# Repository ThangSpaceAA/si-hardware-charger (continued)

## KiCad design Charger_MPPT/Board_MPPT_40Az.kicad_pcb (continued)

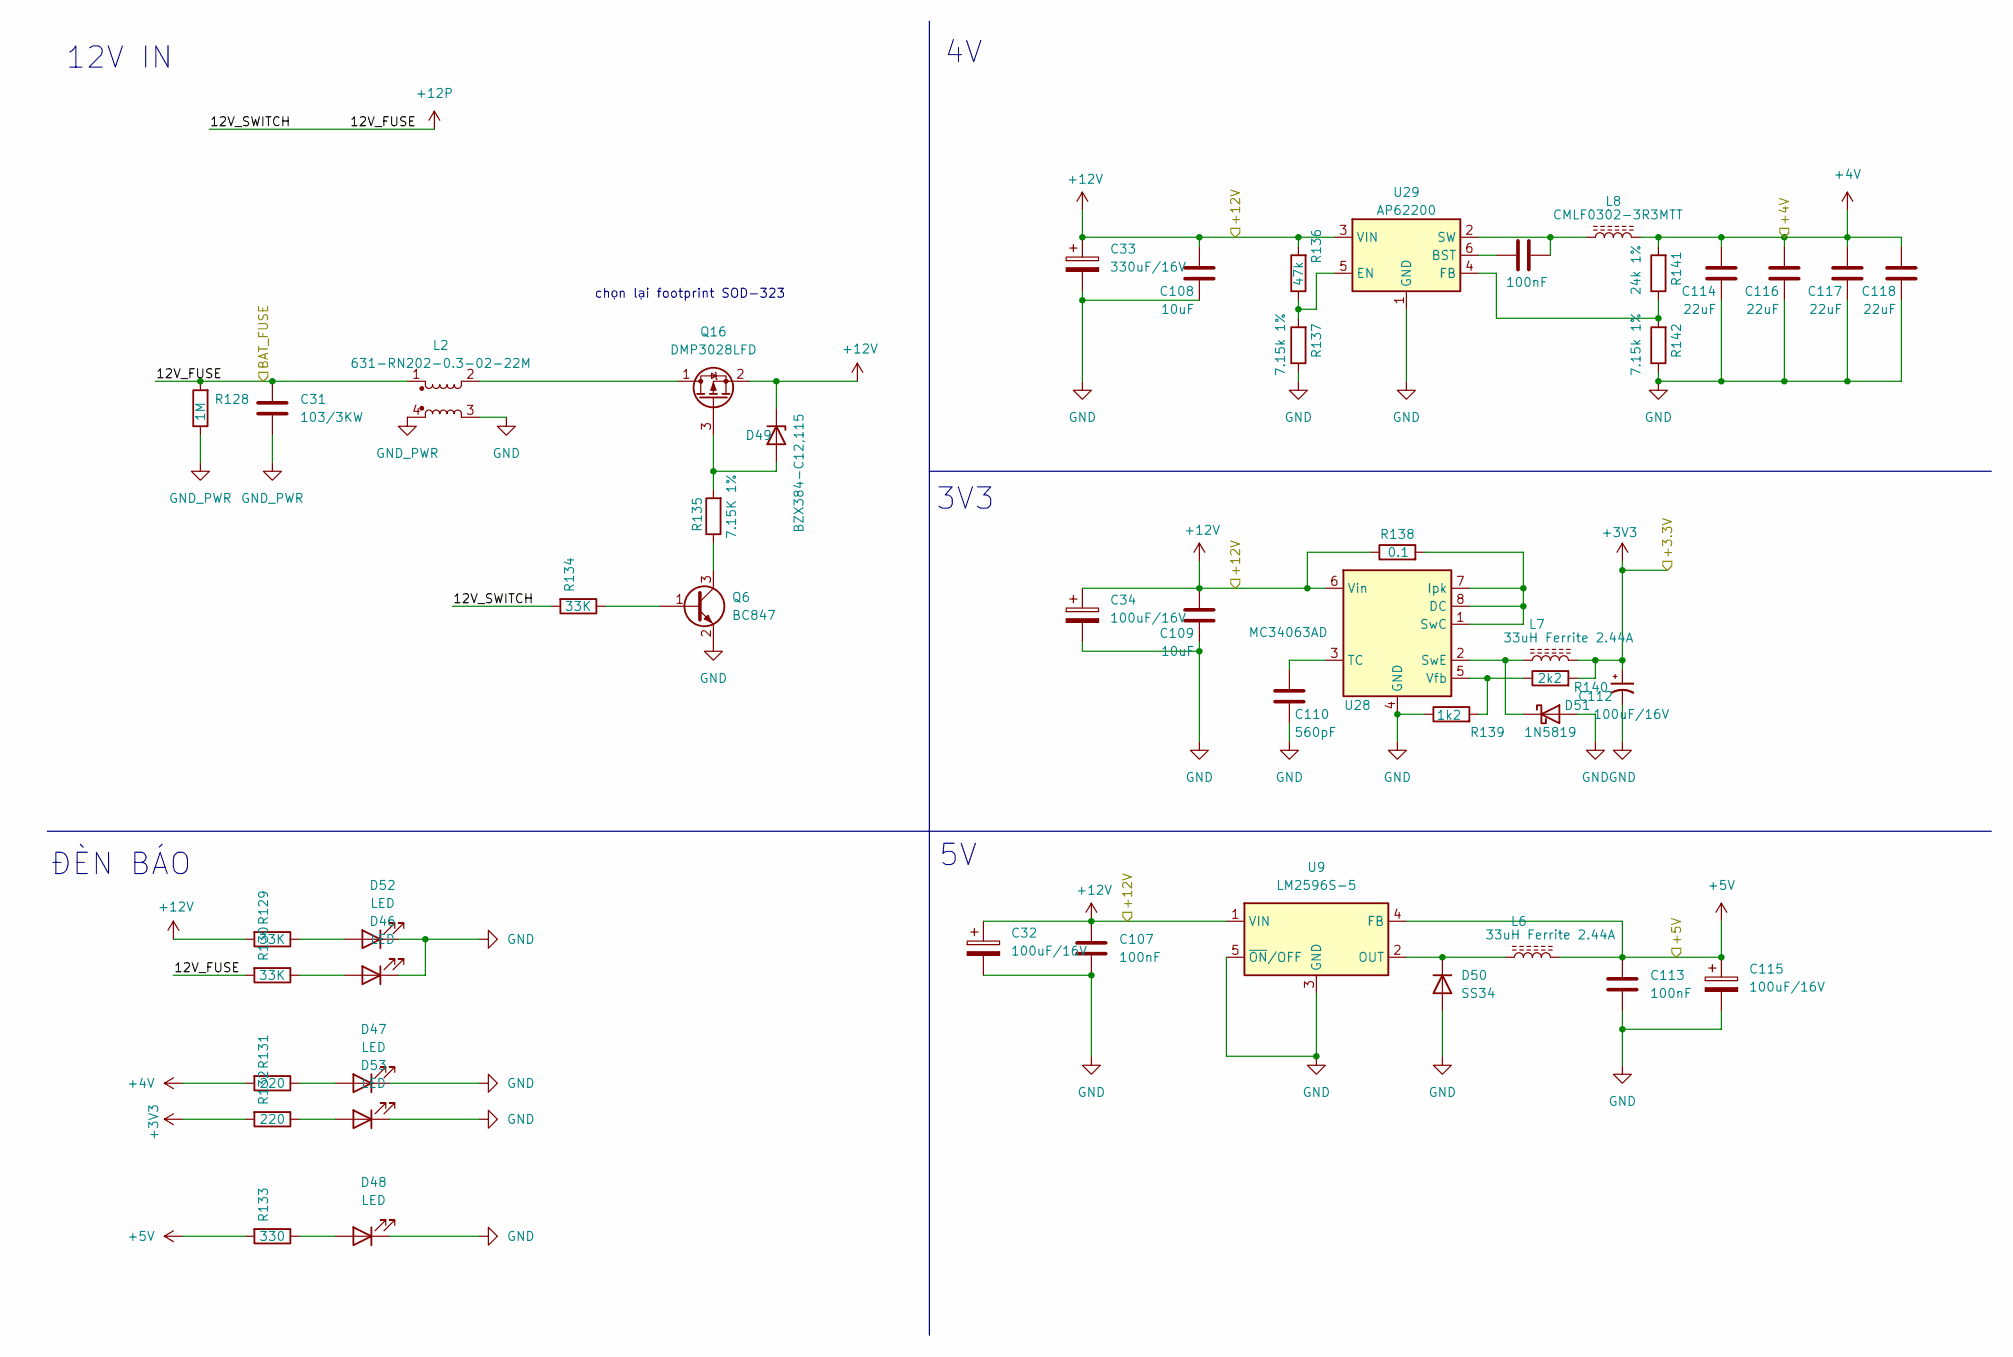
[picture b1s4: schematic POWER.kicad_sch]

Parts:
C31: 103/3KW; C_Disc_D7.0mm_W2.5mm_P5.00mm
C32, C34: 100uF/16V; CP_EIA-6032-28_Kemet-C_Pad2.25x2.35mm_HandSolder
C33: 330uF/16V; CP_EIA-6032-28_Kemet-C_Pad2.25x2.35mm_HandSolder
C107, C111, C113: 100nF; C_0805_2012Metric
C108, C109: 10uF; C_0805_2012Metric
C110: 560pF; C_0805_2012Metric
C112: 100uF/16V; CP_EIA-6032-20_AVX-F_Pad2.25x2.35mm_HandSolder
C114, C116, C117, C118: 22uF; C_0805_2012Metric
C115: 100uF/16V; CP_EIA-6032-15_Kemet-U
D46, D47, D48, D52, D53: LED; LED_0805_2012Metric
D49: BZX384-C12,115; D_SOD-323_HandSoldering
D50: SS34; D_SMA
D51: 1N5819; D_SOD-123F
L2: 631-RN202-0.3-02-22M; Choke_Schaffner_RN202-04-8.8x18.2mm
L6, L7: 33uH Ferrite 2.44A; L_Taiyo-Yuden_NR-60xx
L8: CMLF0302-3R3MTT; L_Wurth_WE-LQSH-3012
Q6: BC847; SOT-23
Q16: DMP3028LFD; TO-252-2
R128: 1M; R_0805_2012Metric
R129, R130, R134: 33K; R_0805_2012Metric
R131, R132: 220; R_0805_2012Metric
R133: 330; R_0805_2012Metric
R135: 7.15K 1%; R_0805_2012Metric
R136: 47k; R_0805_2012Metric
R137, R142: 7.15k 1%; R_0402_1005Metric
R138: 0.1; R_1206_3216Metric
R139: 1k2; R_0805_2012Metric
R140: 2k2; R_0805_2012Metric
R141: 24k 1%; R_0805_2012Metric
U9: LM2596S-5; TO-263-5_TabPin3
U28: MC34063AD; SOIC-8_3.9x4.9mm_P1.27mm
U29: AP62200; TSOT-26

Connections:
+3V3: C112.1, L7.2, R132.2, R140.2; also elsewhere on the board
+4V: C114.1, C116.1, C117.1, C118.1, L8.2, R131.2, R141.2; also elsewhere on the board
+5V: C113.1, C115.1, L6.2, R133.2, U9.4 (FB); also elsewhere on the board
+12V: C32.1, C33.1, C34.1, C107.1, C108.1, C109.1, D49.1 (K), Q16.2 (S), R129.2, R136.2, R138.1, U9.1 (VIN), U28.6 (Vin), U29.3 (VIN); also elsewhere on the board
BAT +: C31.1, L2.1, R128.2, R130.2, R134.2; also elsewhere on the board
GND: C32.2, C33.2, C34.2, C107.2, C108.2, C109.2, C110.2, C112.2, C113.2, C114.2, C115.2, C116.2, C117.2, C118.2, D46.1 (K), D47.1 (K), D48.1 (K), D50.2 (A), D51.2 (A), D52.1 (K), D53.1 (K), L2.3, Q6.2 (E), R137.1, R139.1, R142.1, U9.3 (GND), U9.5 (~ON/OFF), U28.4 (GND), U29.1 (GND); also elsewhere on the board
GND_PWR: C31.2, L2.4, R128.1
unnamed: D46.2 (A), R130.1
unnamed: D47.2 (A), R131.1
unnamed: D48.2 (A), R133.1
unnamed: D49.2 (A), Q16.3 (G), R135.2
unnamed: D50.1 (K), L6.1, U9.2 (OUT)
unnamed: D51.1 (K), L7.1, U28.2 (SwE)
unnamed: D52.2 (A), R129.1
unnamed: D53.2 (A), R132.1
unnamed: Q6.1 (B), R134.1
unnamed: Q6.3 (C), R135.1
unnamed: L2.2, Q16.1 (D)
unnamed: R138.2, U28.1 (SwC), U28.7 (Ipk), U28.8 (DC)
unnamed: C110.1, U28.3 (TC)
unnamed: R139.2, R140.1, U28.5 (Vfb)
unnamed: C111.2, U29.6 (BST)
unnamed: R136.1, R137.2, U29.5 (EN)
unnamed: R141.1, R142.2, U29.4 (FB)
unnamed: C111.1, L8.1, U29.2 (SW)

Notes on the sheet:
12V IN
chọn lại footprint SOD-323
3V3
ĐÈN BÁO

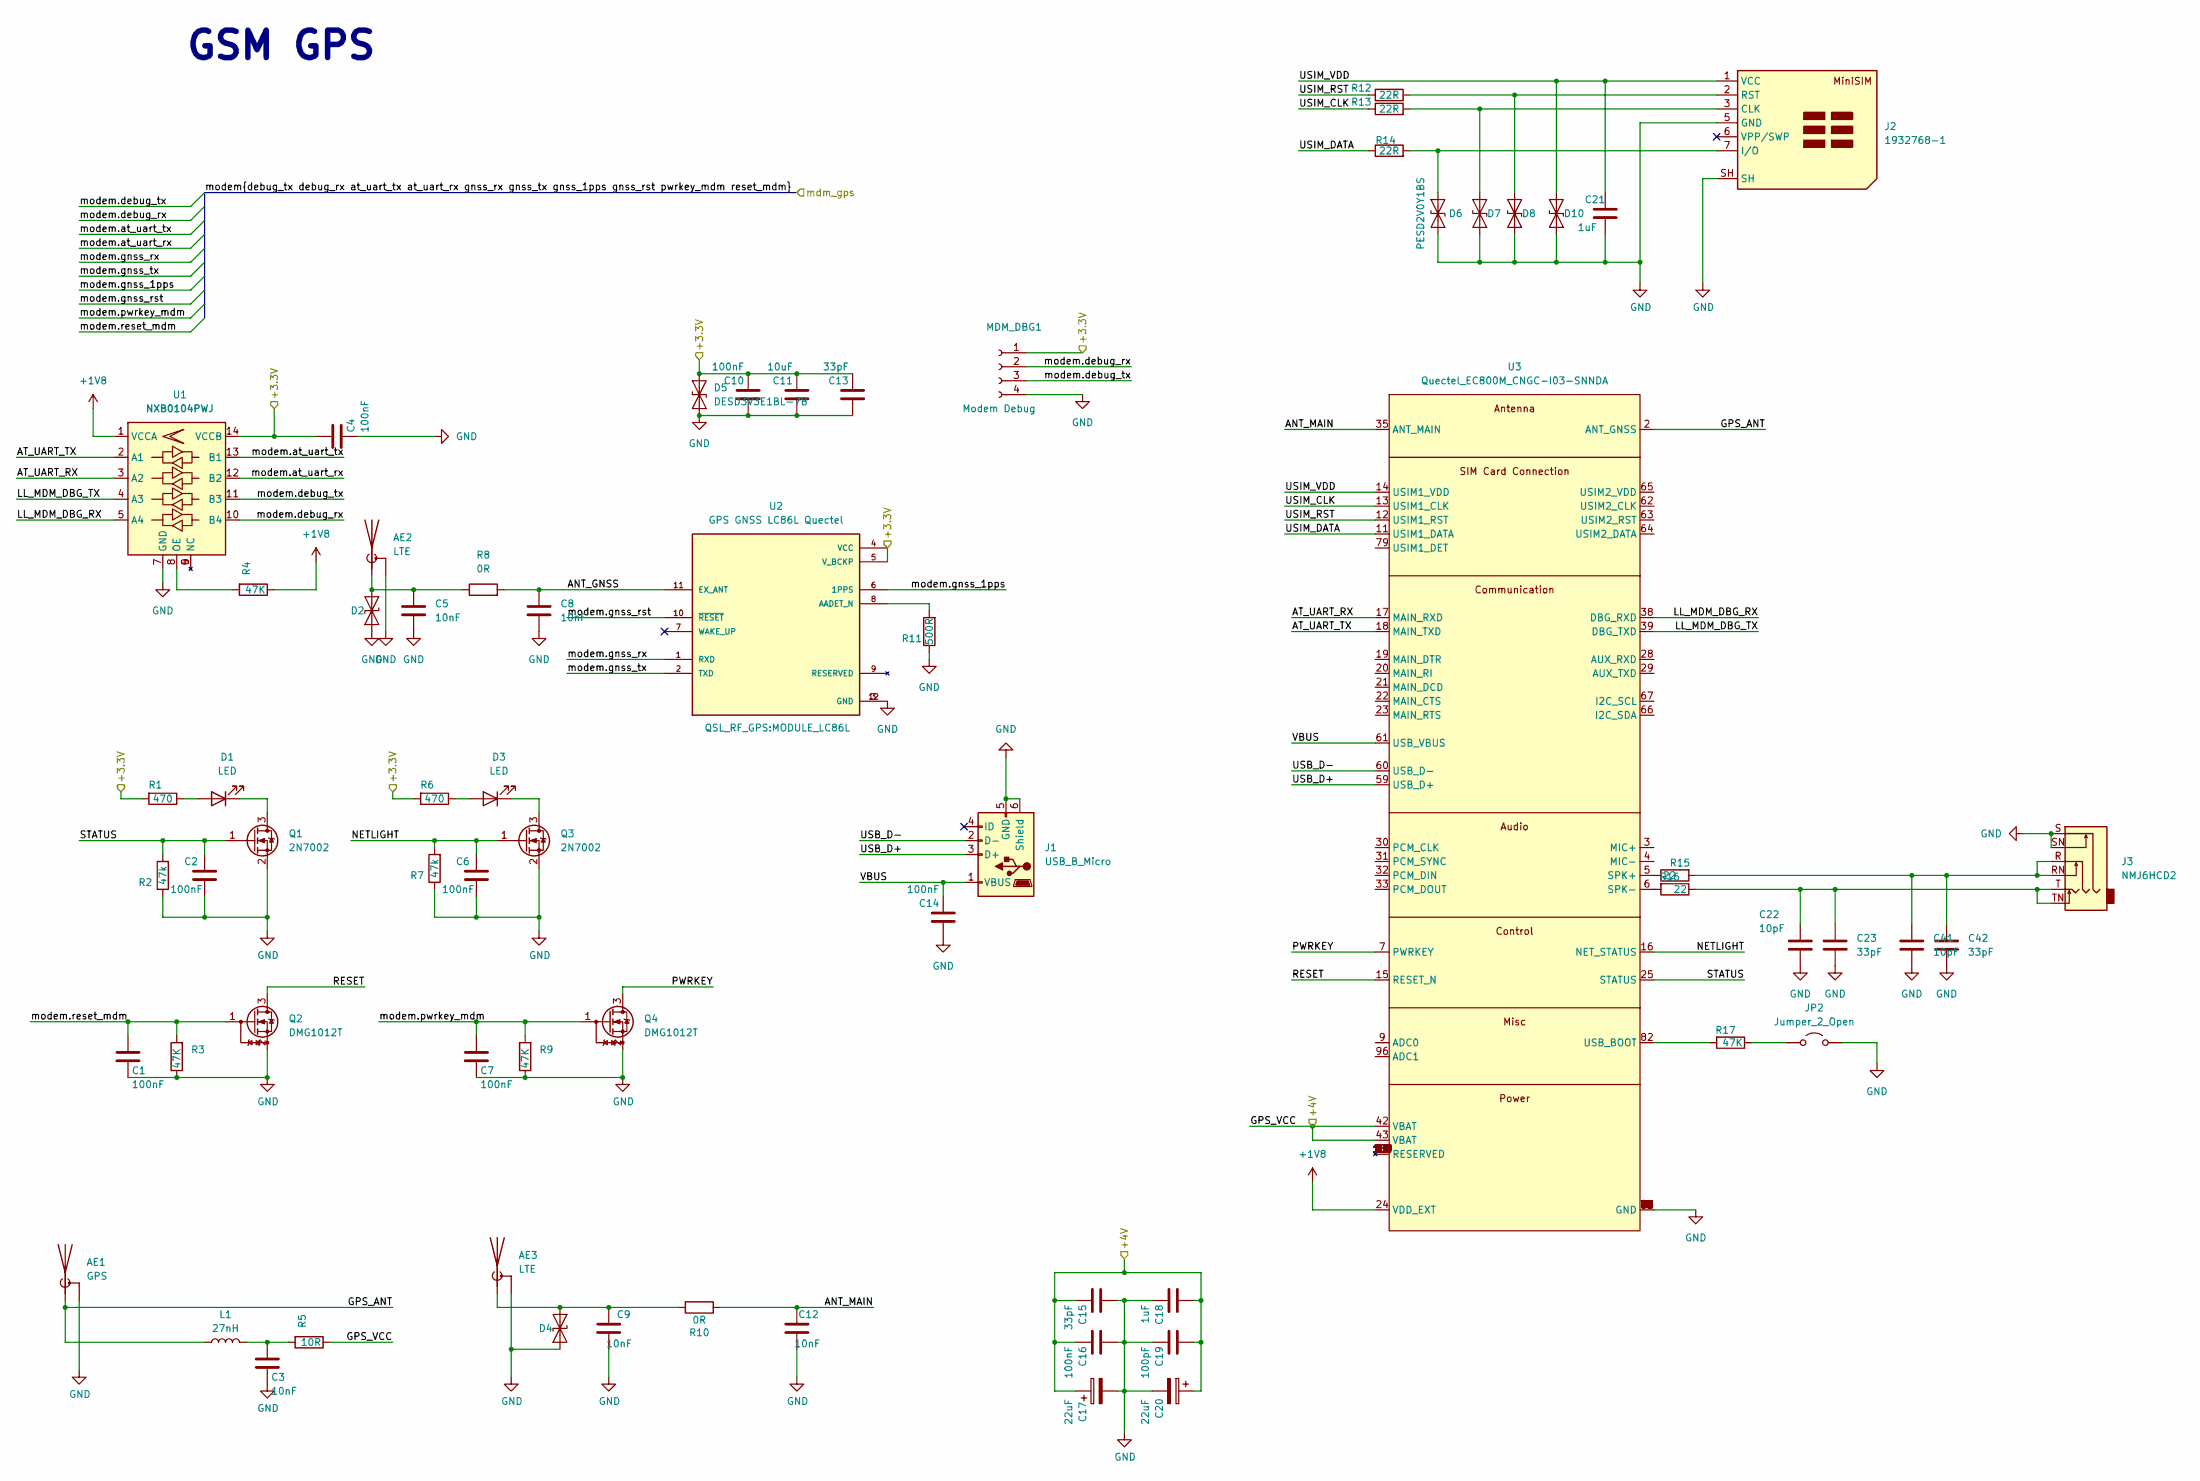
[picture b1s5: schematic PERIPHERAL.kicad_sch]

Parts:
AE1: GPS; SMA_Amphenol_132289_EdgeMount
AE2: LTE; SMA_Amphenol_A-4JA
AE3: LTE; SMA_Amphenol_132289_EdgeMount
C1, C2, C4, C6, C7, C10, C14, C16: 100nF; C_0805_2012Metric
C3, C9, C12: 10nF; C_0805_2012Metric
C5, C8: 10nF; C_0603_1608Metric
C11: 10uF; C_0805_2012Metric
C13, C15: 33pF; C_0805_2012Metric
C17, C20: 22uF; CP_EIA-3216-12_Kemet-S
C18, C21: 1uF; C_0805_2012Metric
C19: 100pF; C_0805_2012Metric
C22, C41: 10pF; C_0603_1608Metric
C23, C42: 33pF; C_0603_1608Metric
D1, D3: LED; LED_0805_2012Metric
D2, D4, D6, D7, D8, D10: PESD2V0Y1BS; D_0201_0603Metric
D5: DESD3V3E1BL-7B; CTS_D_0402_1005Metric
J1: USB_B_Micro; USB_Micro-B_Amphenol_10118194_Horizontal
J2: 1932768-1; nanoSIM_Hinged_CUI_NSIM-2-C
J3: NMJ6HCD2; Jack_3.5mm_CUI_SJ2-3593D-SMT_Horizontal
JP2: Jumper_2_Open; SolderJumper-2_P1.3mm_Open_Pad1.0x1.5mm
L1: 27nH; L_0603_1608Metric
MDM_DBG1: Modem Debug; Molex_PicoBlade_53047-0410_1x04_P1.25mm_Vertical
Q1, Q3: 2N7002; SOT-23
Q2, Q4: DMG1012T; SOT-523
R1, R6: 470; R_0805_2012Metric
R2, R7: 47k; R_0805_2012Metric
R3, R4, R9, R17: 47K; R_0805_2012Metric
R5: 10R; R_0805_2012Metric
R8: 0R; R_0603_1608Metric
R10: 0R; R_0805_2012Metric
R11: 500R; R_0805_2012Metric
R12, R13, R14: 22R; R_0805_2012Metric
R15, R16: 22; R_0603_1608Metric
U1: NXB0104PWJ; TSSOP-14-1EP_4.4x5mm_P0.65mm
U2: GPS GNSS LC86L Quectel; MODULE_LC86L; PARTREV V1.2
U3: Quectel_EC800M_CNGC-I03-SNNDA; Quectel_EC800M_CN

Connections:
+1V8: R4.1, U1.1 (VCCA), U3.24 (VDD_EXT)
+3V3: C4.1, C10.2, C11.2, C13.2, D5.2 (A2), MDM_DBG1.1, R1.2, R6.2, U1.14 (VCCB), U2.4 (VCC), U2.5 (V_BCKP); also elsewhere on the board
+4V: C15.2, C16.2, C17.1, C18.1, C19.1, C20.1, R5.1, U3.42 (VBAT), U3.43 (VBAT); also elsewhere on the board
/MCU/modem.at_uart_rx: U1.12 (B2); also elsewhere on the board
/MCU/modem.at_uart_tx: U1.13 (B1); also elsewhere on the board
/MCU/modem.debug_rx: MDM_DBG1.2, U1.10 (B4)
/MCU/modem.debug_tx: MDM_DBG1.3, U1.11 (B3)
/MCU/modem.gnss_1pps: U2.6 (1PPS); also elsewhere on the board
/MCU/modem.gnss_rst: U2.10 (~RESET); also elsewhere on the board
/MCU/modem.gnss_rx: U2.1 (RXD); also elsewhere on the board
/MCU/modem.gnss_tx: U2.2 (TXD); also elsewhere on the board
/MCU/modem.pwrkey_mdm: C7.1, Q4.1 (G), R9.2; also elsewhere on the board
/MCU/modem.reset_mdm: C1.1, Q2.1 (G), R3.2; also elsewhere on the board
/MDM_SIM/ANT_GNSS: C8.1, R8.2, U2.11 (EX_ANT)
/MDM_SIM/ANT_MAIN: C12.2, R10.1, U3.35 (ANT_MAIN)
/MDM_SIM/AT_UART_RX: U1.3 (A2), U3.17 (MAIN_RXD)
/MDM_SIM/AT_UART_TX: U1.2 (A1), U3.18 (MAIN_TXD)
/MDM_SIM/GPS_ANT: AE1.1 (A), L1.1, U3.2 (ANT_GNSS)
/MDM_SIM/LL_MDM_DBG_RX: U1.5 (A4), U3.38 (DBG_RXD)
/MDM_SIM/LL_MDM_DBG_TX: U1.4 (A3), U3.39 (DBG_TXD)
/MDM_SIM/NETLIGHT: C6.2, Q3.1 (G), R7.2, U3.16 (NET_STATUS)
/MDM_SIM/PWRKEY: Q4.3 (D), U3.7 (PWRKEY)
/MDM_SIM/RESET: Q2.3 (D), U3.15 (RESET_N)
/MDM_SIM/STATUS: C2.2, Q1.1 (G), R2.2, U3.25 (STATUS)
/MDM_SIM/USB_D+: J1.3 (D+), U3.59 (USB_D+)
/MDM_SIM/USB_D-: J1.2 (D-), U3.60 (USB_D-)
/MDM_SIM/USIM_CLK: R13.1, U3.13 (USIM1_CLK)
/MDM_SIM/USIM_DATA: R14.1, U3.11 (USIM1_DATA)
/MDM_SIM/USIM_RST: R12.1, U3.12 (USIM1_RST)
/MDM_SIM/USIM_VDD: C21.2, D10.2 (A2), J2.1 (VCC), U3.14 (USIM1_VDD)
/MDM_SIM/VBUS: C14.2, J1.1 (VBUS), U3.61 (USB_VBUS)
GND: AE1.2 (Shield), AE2.2 (Shield), AE3.2 (Shield), C1.2, C2.1, C3.2, C4.2, C5.2, C6.1, C7.2, C8.2, C9.1, C10.1, C11.1, C12.1, C13.1, C14.1, C15.1, C16.1, C17.2, C18.2, C19.2, C20.2, C21.1, C22.2, C23.2, C41.2, C42.2, D2.1 (A1), D4.1 (A1), D5.1 (A1), D6.1 (A1), D7.1 (A1), D8.1 (A1), D10.1 (A1), J1.5 (GND), J1.6 (Shield), J2.5 (GND), J2.SH, J3.S, J3.SN, JP2.2 (B), MDM_DBG1.4, Q1.2 (S), Q2.2 (S), Q3.2 (S), Q4.2 (S), R2.1, R3.1, R7.1, R9.1, R11.1, U1.7 (GND), U2.3 (GND), U2.12 (GND), U3.1 (GND), U3.10 (GND), U3.27 (GND), U3.34 (GND), U3.36 (GND), U3.37 (GND), U3.40 (GND), U3.41 (GND), U3.45 (GND), U3.46 (GND), U3.47 (GND), U3.48 (GND), U3.70 (GND), U3.71 (GND), U3.72 (GND), U3.73 (GND), U3.88 (GND), U3.89 (GND), U3.90 (GND), U3.91 (GND), U3.92 (GND), U3.93 (GND), U3.94 (GND), U3.95 (GND); also elsewhere on the board
unnamed: AE2.1 (A), C5.1, D2.2 (A2), R8.1
unnamed: AE3.1 (A), C9.2, D4.2 (A2), R10.2
unnamed: C3.1, L1.2, R5.2
unnamed: C22.1, C23.1, J3.T, J3.TN, R16.1
unnamed: C41.1, C42.1, J3.R, J3.RN, R15.2
unnamed: D1.2 (A), R1.1
unnamed: D1.1 (K), Q1.3 (D)
unnamed: D3.2 (A), R6.1
unnamed: D3.1 (K), Q3.3 (D)
unnamed: D6.2 (A2), J2.7 (I/O), R14.2
unnamed: D7.2 (A2), J2.3 (CLK), R13.2
unnamed: D8.2 (A2), J2.2 (RST), R12.2
unnamed: JP2.1 (A), R17.1
unnamed: R4.2, U1.8 (OE)
unnamed: R11.2, U2.8 (AADET_N)
unnamed: R15.1, U3.5 (SPK+)
unnamed: R16.2, U3.6 (SPK-)
unnamed: R17.2, U3.82 (USB_BOOT)

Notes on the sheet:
GSM GPS

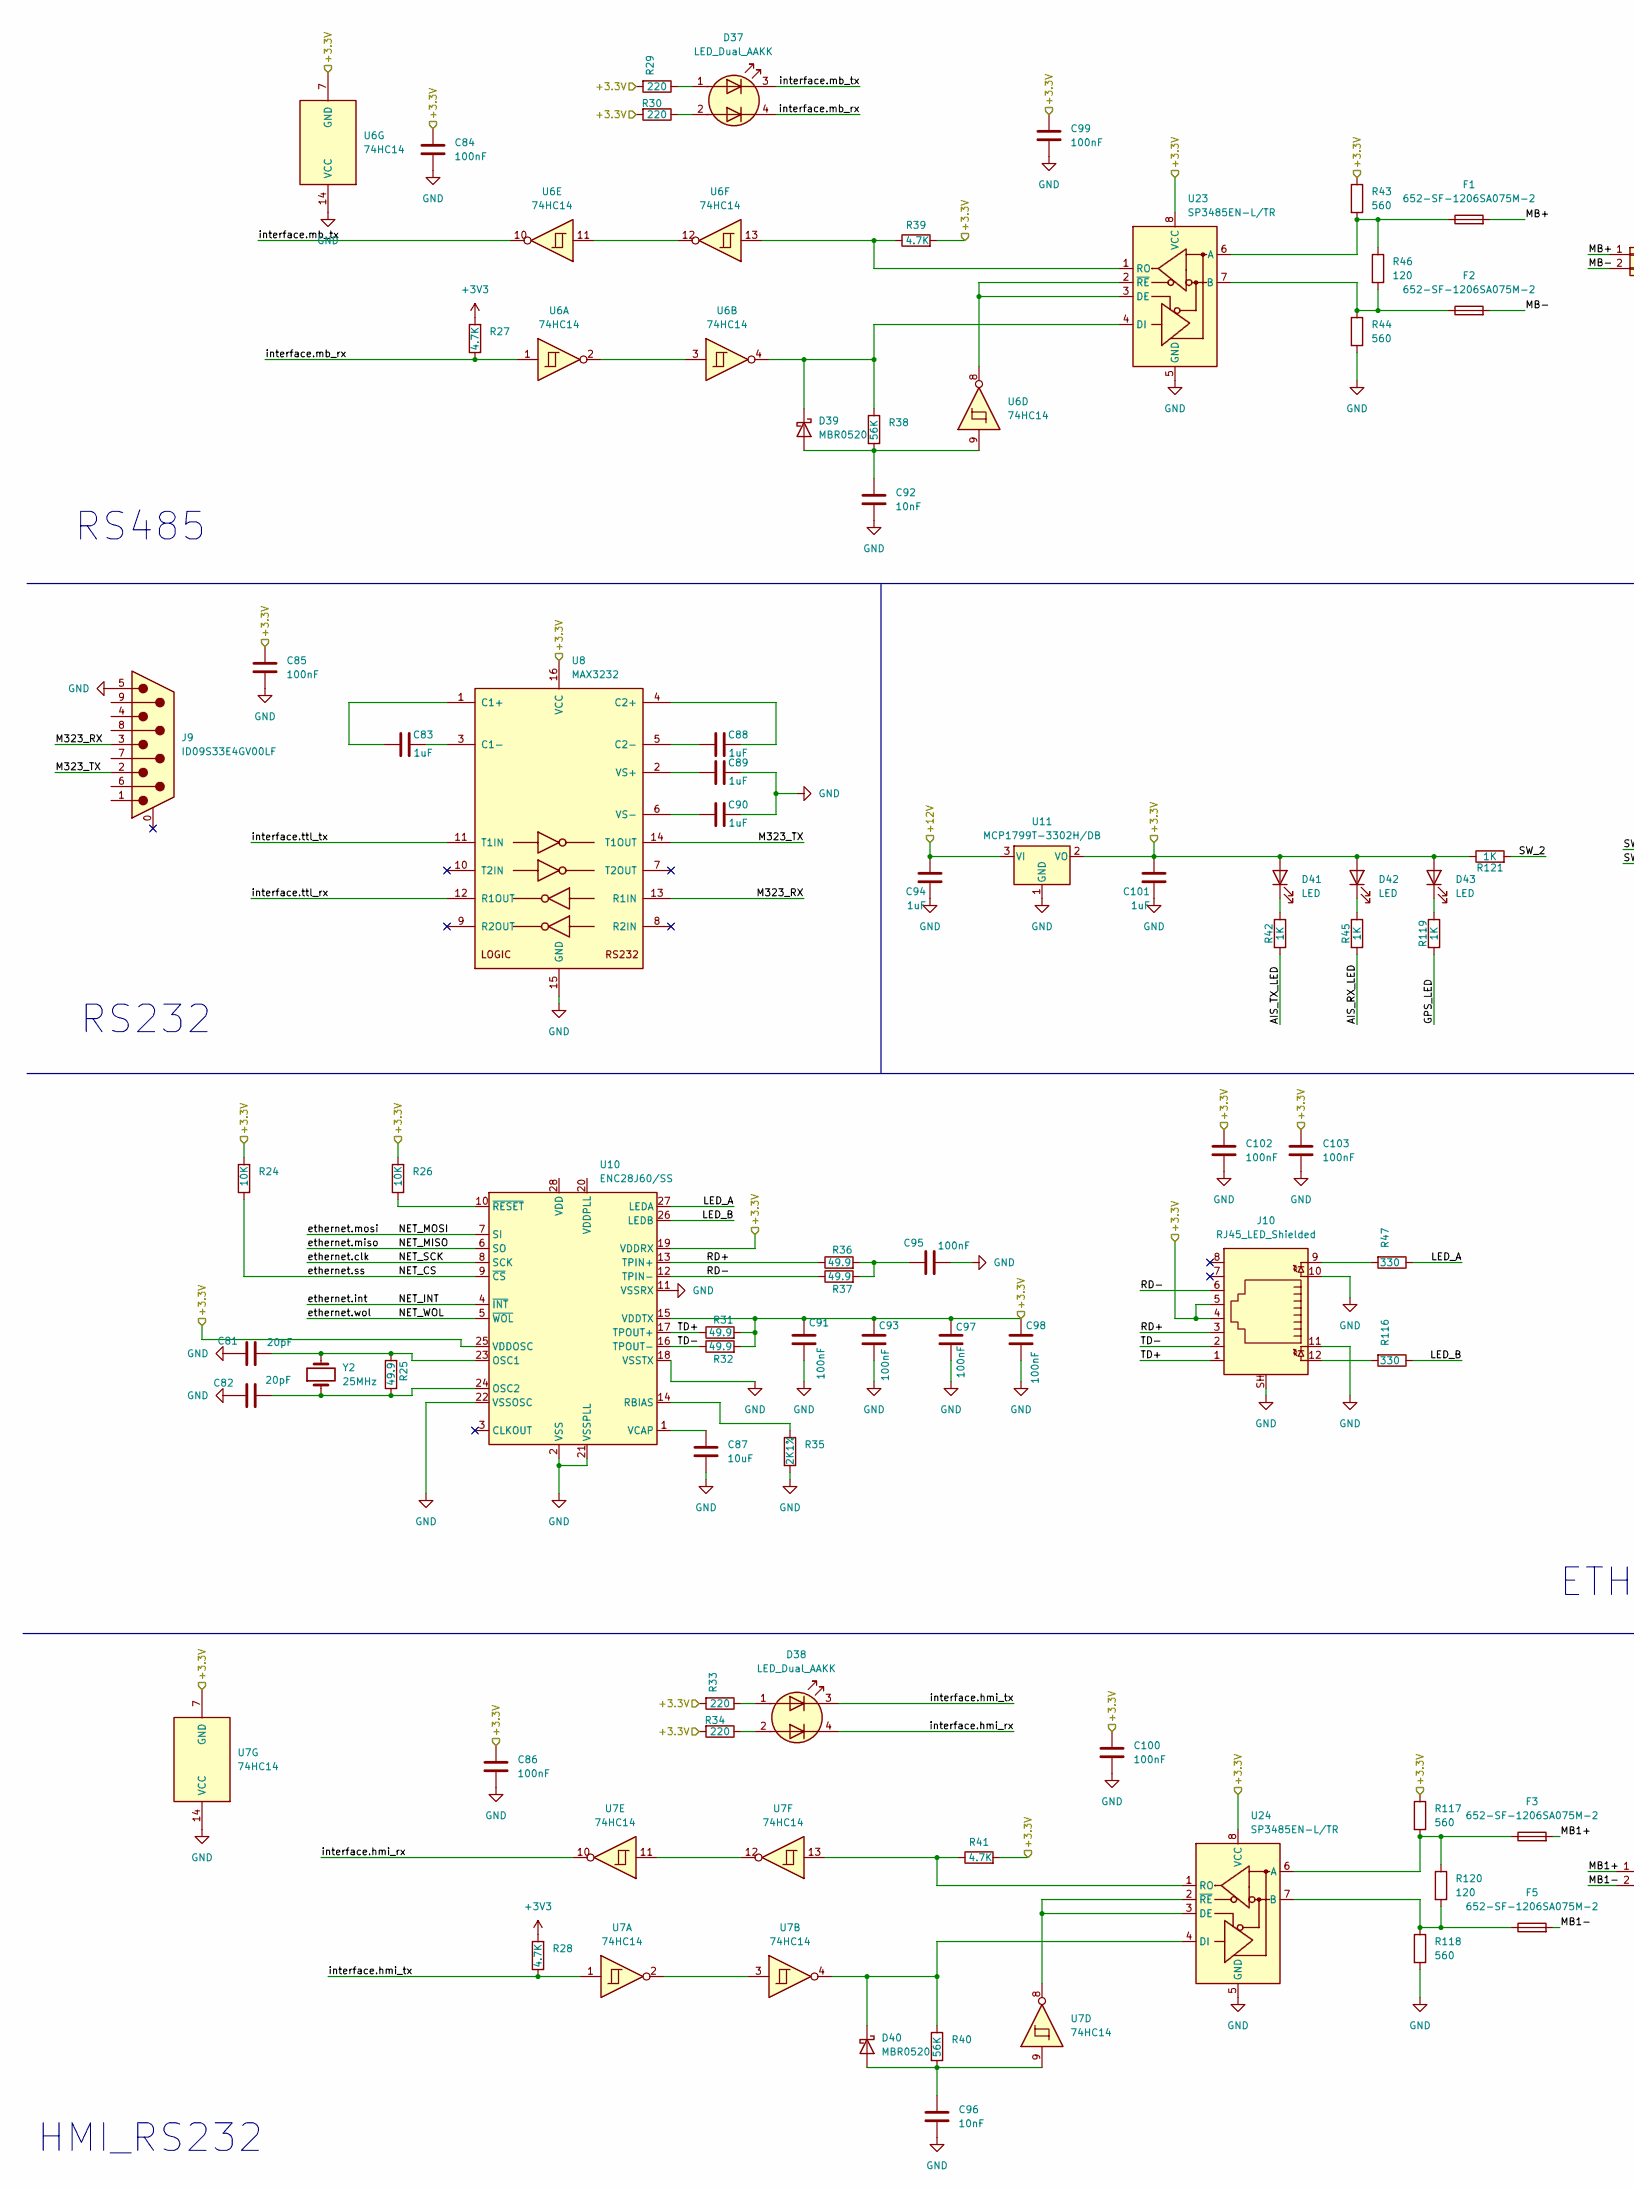
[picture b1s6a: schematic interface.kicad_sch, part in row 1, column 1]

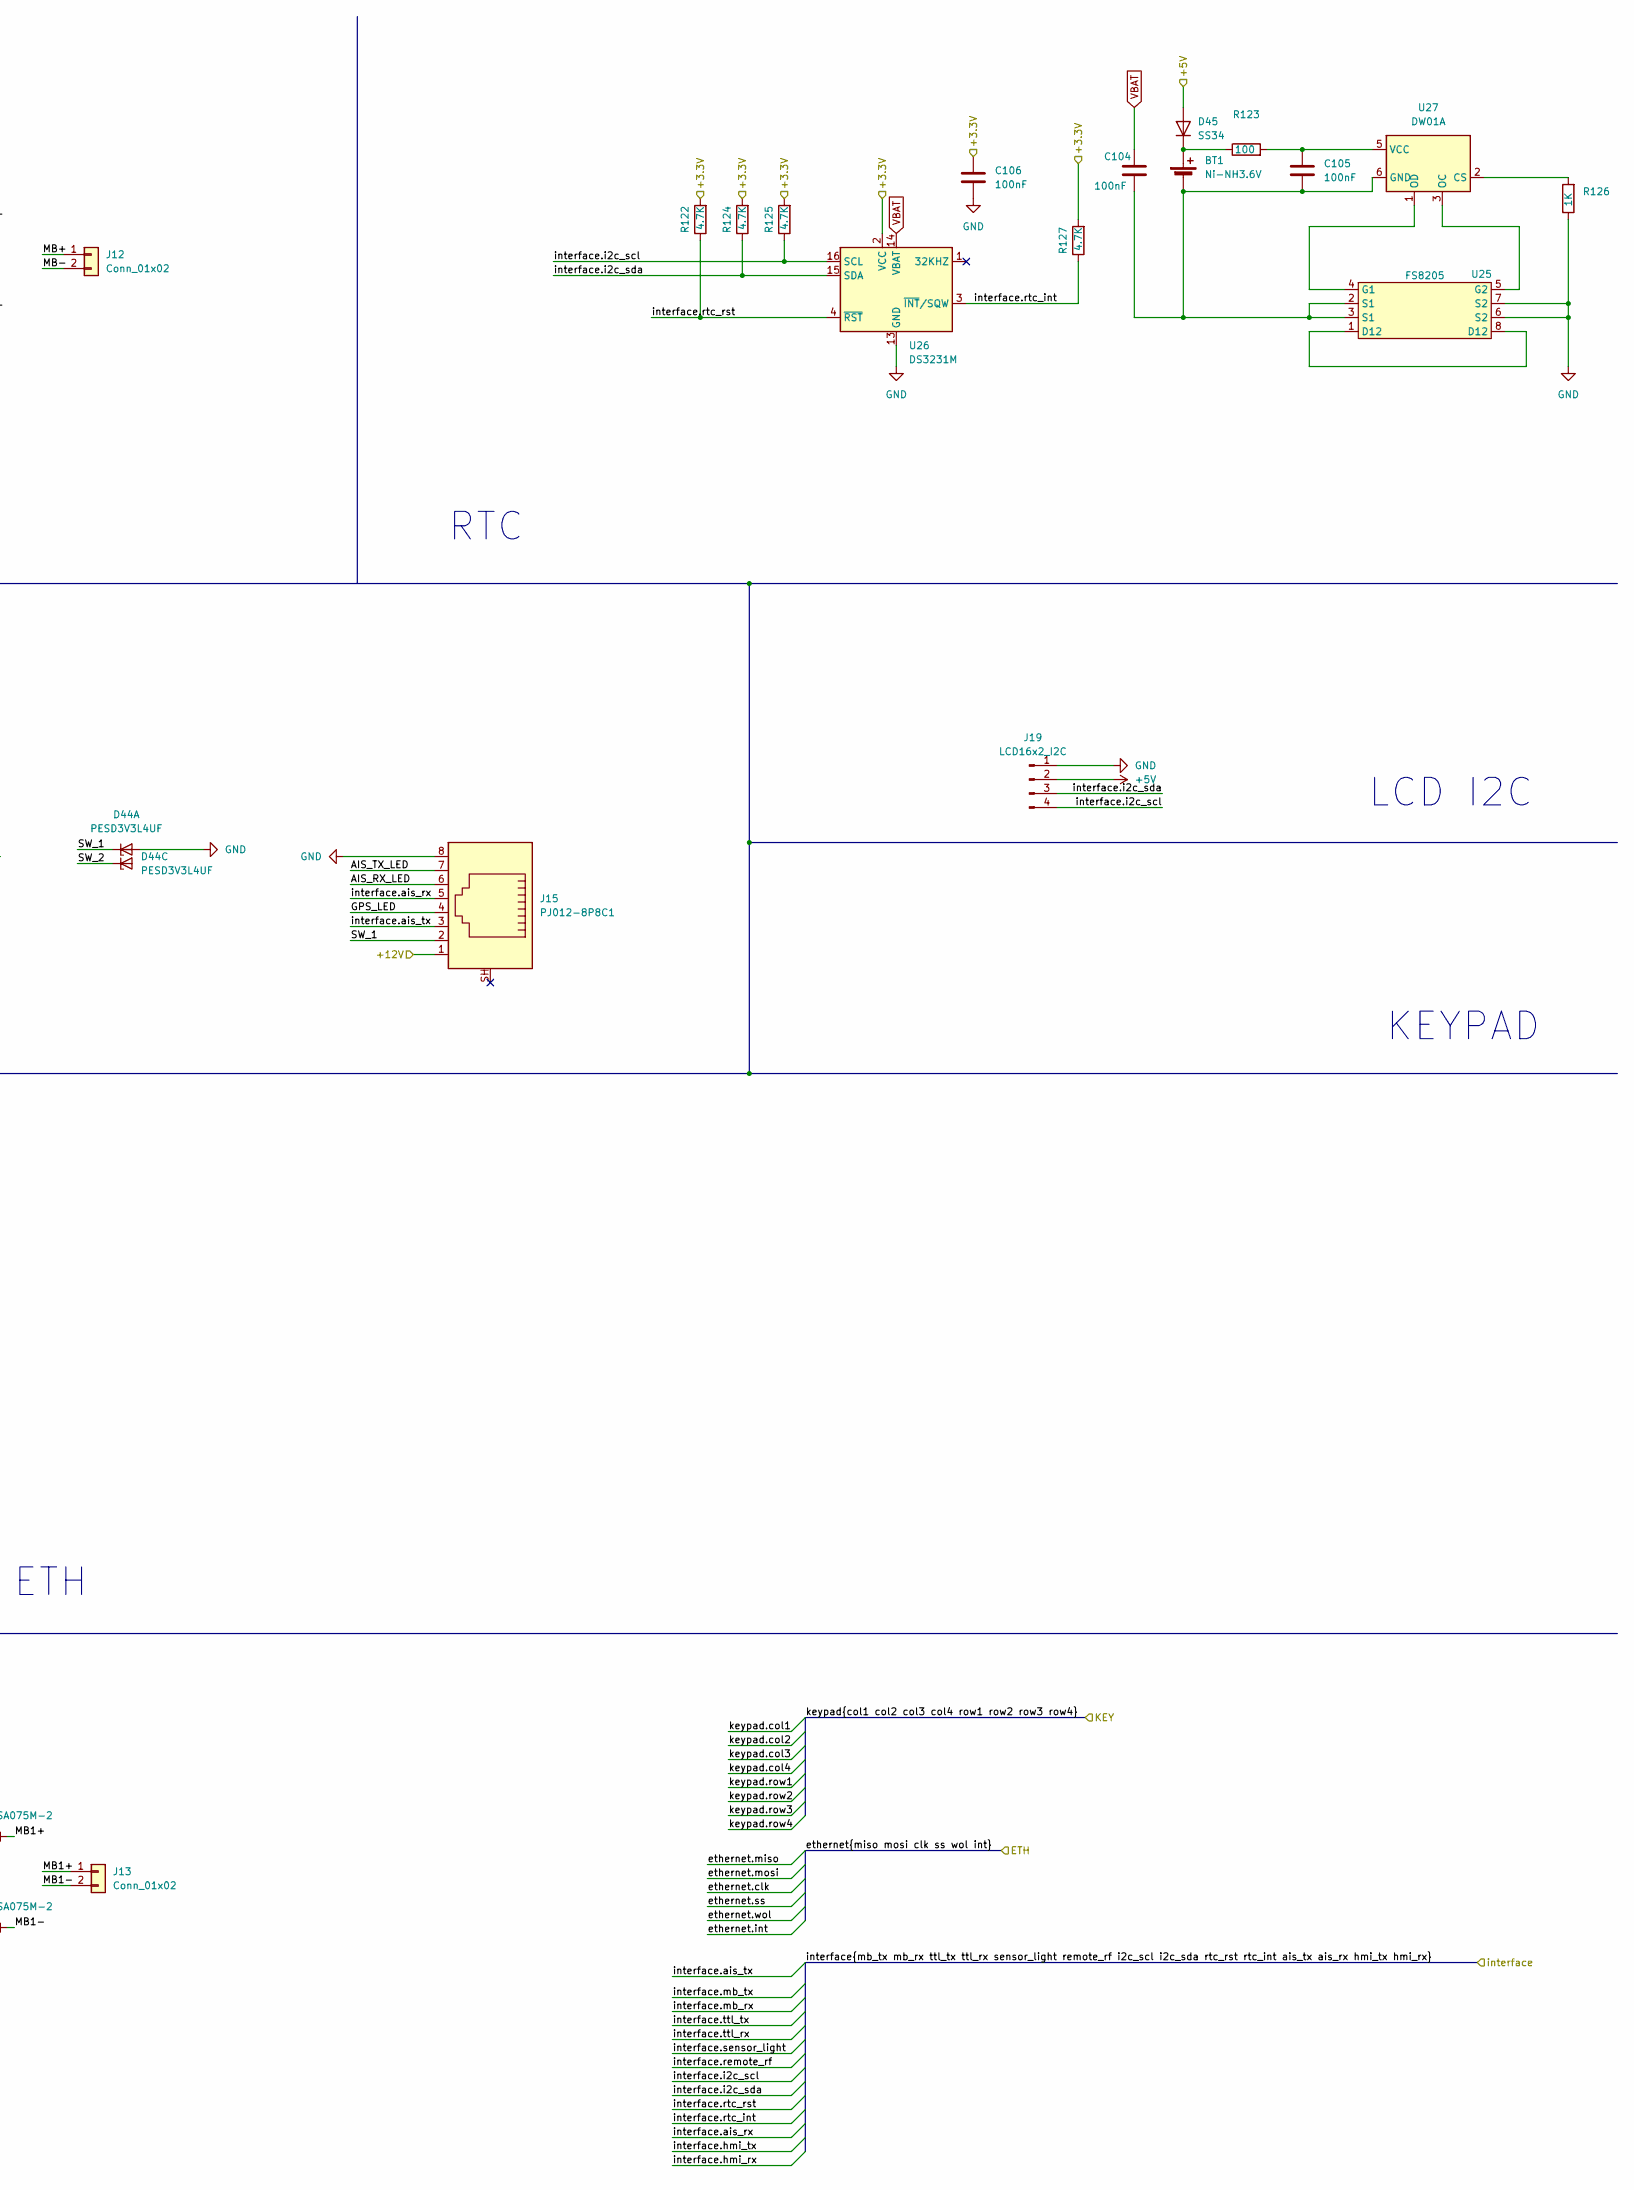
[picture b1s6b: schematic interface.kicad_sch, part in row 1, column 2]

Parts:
BT1: Ni-NH3.6V; NI-NH3.6V
C81, C82: 20pF; C_0402_1005Metric
C83, C88, C89, C90, C94, C101: 1uF; C_0805_2012Metric
C84, C85, C86, C91, C93, C95, C97, C98, C99, C100, C102, C103, C104, C105, C106: 100nF; C_0805_2012Metric
C87: 10uF; C_0805_2012Metric
C92, C96: 10nF; C_0805_2012Metric
D37, D38: LED_Dual_AAKK; LED_D3.0mmP2.54_2x2_Horizontal__ACAC
D39, D40: MBR0520; D_SOD-123
D41, D42, D43: LED; LED_0805_2012Metric
D44: PESD3V3L4UF; SOT-886
D45: SS34; D_SMA
F1, F2, F3, F5: 652-SF-1206SA075M-2; Fuse_1812_4532Metric
J9: ID09S33E4GV00LF; DSUB-9_Female_Horizontal_P2.77x2.84mm_EdgePinOffset4.94mm_H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
J10: RJ45_LED_Shielded; RJ45_Hanrun_HR911105A_Horizontal
J12, J13: Conn_01x02; TerminalBlock_Phoenix_MKDS-1,5-2-5.08_1x02_P5.08mm_Horizont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
J15: PJ012-8P8C1; RJ45_OST_PJ012-8P8CX_Vertical
J19: LCD16x2_I2C; PinHeader_1x04_P2.54mm_Vertical
R24, R26: 10K; R_0805_2012Metric
R25, R31, R32, R36, R37: 49.9; R_0805_2012Metric
R27, R28, R39, R41, R122, R124, R125, R127: 4.7K; R_0805_2012Metric
R29, R30, R33, R34: 220; R_0805_2012Metric
R35: 2K1%; R_0805_2012Metric
R38, R40: 56K; R_0805_2012Metric
R42, R45, R119, R121, R126: 1K; R_0805_2012Metric
R43, R44, R117, R118: 560; R_0805_2012Metric
R46, R120: 120; R_1206_3216Metric
R47, R116: 330; R_0805_2012Metric
R123: 100; R_0805_2012Metric
U6, U7: 74HC14; SOIC-14_3.9x8.7mm_P1.27mm
U8: MAX3232; SOP-16_3.9x9.9mm_P1.27mm
U10: ENC28J60/SS; SOIC-28W_7.5x17.9mm_P1.27mm
U11: MCP1799T-3302H/DB; SOT-23
U23, U24: SP3485EN-L/TR; SOIC-8_3.9x4.9mm_P1.27mm
U25: FS8205; TSSOP-8_4.4x3mm_P0.65mm
U26: DS3231M; SOIC-16W_7.5x10.3mm_P1.27mm
U27: DW01A; SOT-23-6
Y2: 25MHz; Crystal_SMD_Qantek_QC5CB-2Pin_5x3.2mm

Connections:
+3V3: C84.1, C85.1, C86.1, C91.1, C93.1, C97.1, C98.1, C99.1, C100.1, C101.1, C102.1, C103.1, C106.1, D41.2 (A), D42.2 (A), D43.2 (A), J10.4, J10.5, R24.2, R26.2, R27.2, R28.2, R29.2, R30.2, R31.2, R32.2, R33.2, R34.2, R39.2, R41.2, R43.1, R117.1, R121.1, R122.2, R124.2, R125.2, R127.2, U6.7 (GND), U7.7 (GND), U8.16 (VCC), U10.15 (VDDTX), U10.19 (VDDRX), U10.25 (VDDOSC), U11.2 (VO), U23.8 (VCC), U24.8 (VCC), U26.2 (VCC); also elsewhere on the board
+5V: D45.2 (A), J19.2; also elsewhere on the board
/INTERFACE/+12V: C94.1, J15.1, U11.3 (VI)
/INTERFACE/AIS_RX_LED: J15.6, R45.2
/INTERFACE/AIS_TX_LED: J15.7, R42.2
/INTERFACE/GPS_LED: J15.4, R119.2
/INTERFACE/LED_A: R47.1, U10.27 (LEDA)
/INTERFACE/LED_B: R116.1, U10.26 (LEDB)
/INTERFACE/M323_RX: J9.3, U8.13 (R1IN)
/INTERFACE/M323_TX: J9.2, U8.14 (T1OUT)
/INTERFACE/MB1+: F3.2, J13.1
/INTERFACE/MB1-: F5.2, J13.2
/INTERFACE/MB+: F1.2, J12.1
/INTERFACE/MB-: F2.2, J12.2
/INTERFACE/RD+: J10.3, R36.1, U10.13 (TPIN+)
/INTERFACE/RD-: J10.6, R37.1, U10.12 (TPIN-)
/INTERFACE/SW_1: D44.1 (K1), J15.2
/INTERFACE/SW_2: D44.4 (K3), R121.2
/INTERFACE/TD+: J10.1, R31.1, U10.17 (TPOUT+)
/INTERFACE/TD-: J10.2, R32.1, U10.16 (TPOUT-)
/INTERFACE/ethernet.clk: U10.8 (SCK); also elsewhere on the board
/INTERFACE/ethernet.int: U10.4 (~INT); also elsewhere on the board
/INTERFACE/ethernet.miso: U10.6 (SO); also elsewhere on the board
/INTERFACE/ethernet.mosi: U10.7 (SI); also elsewhere on the board
/INTERFACE/ethernet.ss: R24.1, U10.9 (~CS); also elsewhere on the board
/INTERFACE/ethernet.wol: U10.5 (~WOL); also elsewhere on the board
/INTERFACE/interface.ais_rx: J15.5; also elsewhere on the board
/INTERFACE/interface.ais_tx: J15.3; also elsewhere on the board
/INTERFACE/interface.hmi_rx: D38.4 (K2), U7.10; also elsewhere on the board
/INTERFACE/interface.hmi_tx: D38.3 (K1), R28.1, U7.1; also elsewhere on the board
/INTERFACE/interface.i2c_scl: J19.4, R125.1, U26.16 (SCL); also elsewhere on the board
/INTERFACE/interface.i2c_sda: J19.3, R124.1, U26.15 (SDA); also elsewhere on the board
/INTERFACE/interface.mb_rx: D37.4 (K2), R27.1, U6.1; also elsewhere on the board
/INTERFACE/interface.mb_tx: D37.3 (K1), U6.10; also elsewhere on the board
/INTERFACE/interface.rtc_int: R127.1, U26.3 (~INT/SQW); also elsewhere on the board
/INTERFACE/interface.rtc_rst: R122.1, U26.4 (~RST); also elsewhere on the board
/INTERFACE/interface.ttl_rx: U8.12 (R1OUT); also elsewhere on the board
/INTERFACE/interface.ttl_tx: U8.11 (T1IN); also elsewhere on the board
GND: C81.1, C82.1, C84.2, C85.2, C86.2, C87.2, C89.2, C90.2, C91.2, C92.2, C93.2, C94.2, C95.2, C96.2, C97.2, C98.2, C99.2, C100.2, C101.2, C102.2, C103.2, C106.2, D44.2 (A), D44.5 (A), J9.5, J10.10, J10.11, J10.SH, J15.8, J19.1, R35.2, R44.2, R118.2, R126.1, U6.14 (VCC), U7.14 (VCC), U8.15 (GND), U10.2 (VSS), U10.11 (VSSRX), U10.18 (VSSTX), U10.21 (VSSPLL), U10.22 (VSSOSC), U11.1 (GND), U23.5 (GND), U24.5 (GND), U25.6 (S2), U25.7 (S2), U26.5 (GND), U26.6 (GND), U26.7 (GND), U26.8 (GND), U26.9 (GND), U26.10 (GND), U26.11 (GND), U26.12 (GND), U26.13 (GND); also elsewhere on the board
unnamed: BT1.1 (+), D45.1 (K), R123.1
unnamed: BT1.2 (-), C104.2, C105.2, U25.2 (S1), U25.3 (S1), U27.6 (GND)
unnamed: C95.1, R36.2, R37.2
unnamed: D37.1 (A1), R29.1
unnamed: D37.2 (A2), R30.1
unnamed: D38.1 (A1), R33.1
unnamed: D38.2 (A2), R34.1
unnamed: C92.1, D39.2 (A), R38.2, U6.9
unnamed: D39.1 (K), R38.1, U6.4, U23.4 (DI)
unnamed: C96.1, D40.2 (A), R40.2, U7.9
unnamed: D40.1 (K), R40.1, U7.4, U24.4 (DI)
unnamed: D41.1 (K), R42.1
unnamed: D42.1 (K), R45.1
unnamed: D43.1 (K), R119.1
unnamed: J10.9, R47.2
unnamed: J10.12, R116.2
unnamed: U6.2, U6.3
unnamed: U6.11, U6.12
unnamed: U7.2, U7.3
unnamed: U7.11, U7.12
unnamed: C83.1, U8.1 (C1+)
unnamed: C83.2, U8.3 (C1-)
unnamed: C88.2, U8.4 (C2+)
unnamed: C88.1, U8.5 (C2-)
unnamed: C89.1, U8.2 (VS+)
unnamed: C90.1, U8.6 (VS-)
unnamed: C81.2, R25.2, U10.23 (OSC1), Y2.2
unnamed: C82.2, R25.1, U10.24 (OSC2), Y2.1
unnamed: R35.1, U10.14 (RBIAS)
unnamed: C87.1, U10.1 (VCAP)
unnamed: R26.1, U10.10 (~RESET)
unnamed: F1.1, R43.2, R46.1, U23.6 (A)
unnamed: F2.1, R44.1, R46.2, U23.7 (B)
unnamed: U6.8, U23.2 (~RE), U23.3 (DE)
unnamed: R39.1, U6.13, U23.1 (RO)
unnamed: F3.1, R117.2, R120.1, U24.6 (A)
unnamed: F5.1, R118.1, R120.2, U24.7 (B)
unnamed: U7.8, U24.2 (~RE), U24.3 (DE)
unnamed: R41.1, U7.13, U24.1 (RO)
unnamed: U25.1 (D12), U25.8 (D12)
unnamed: U25.4 (G1), U27.1 (OD)
unnamed: U25.5 (G2), U27.3 (OC)
unnamed: R126.2, U27.2 (CS)
unnamed: C105.1, R123.2, U27.5 (VCC)
VBAT: C104.1, U26.14 (VBAT)

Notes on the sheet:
RTC
LCD I2C
KEYPAD
RS485
ETH
HMI_RS232
RS232
